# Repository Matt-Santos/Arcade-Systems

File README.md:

# Arcade Systems

A collection of custom hardware, software, and artwork for my arcade projects. It includes several retro-inspired builds using modern hardware as well as a few modifications to repair/improve functionality on older commercial systems. 

As of 2025 my arcade includes the following items:

## Custom Designs
- Pinball Magic (2022)
- Pedistal (2021)
- Countertop (2020)
- Cocktail (2019)

## Commercial Pinballs
- [Secret Service](https://www.ipdb.org/machine.cgi?id=2090) (Data East, 1988)
- [Escape from the Lost World](https://www.ipdb.org/machine.cgi?id=789) (Bally, 1988)
- [Farfalla](https://www.ipdb.org/machine.cgi?id=824) (Zaccaria, 1983)
- [SlugFest](https://www.ipdb.org/machine.cgi?id=3281) (Williams, 1991)
- [Prospector](https://www.ipdb.org/machine.cgi?id=1871) (Segasa, 1977)
- [Captain Fantastic](https://www.ipdb.org/machine.cgi?id=438) (Bally, 1976)
- [Geisha](https://www.ipdb.org/machine.cgi?id=994) (Playmatic, 1973)

## Jukeboxes
- Rockola 488 Sunset Gold (Rockola, 1982)
- Satellite 200 (NSM Music, 1982)

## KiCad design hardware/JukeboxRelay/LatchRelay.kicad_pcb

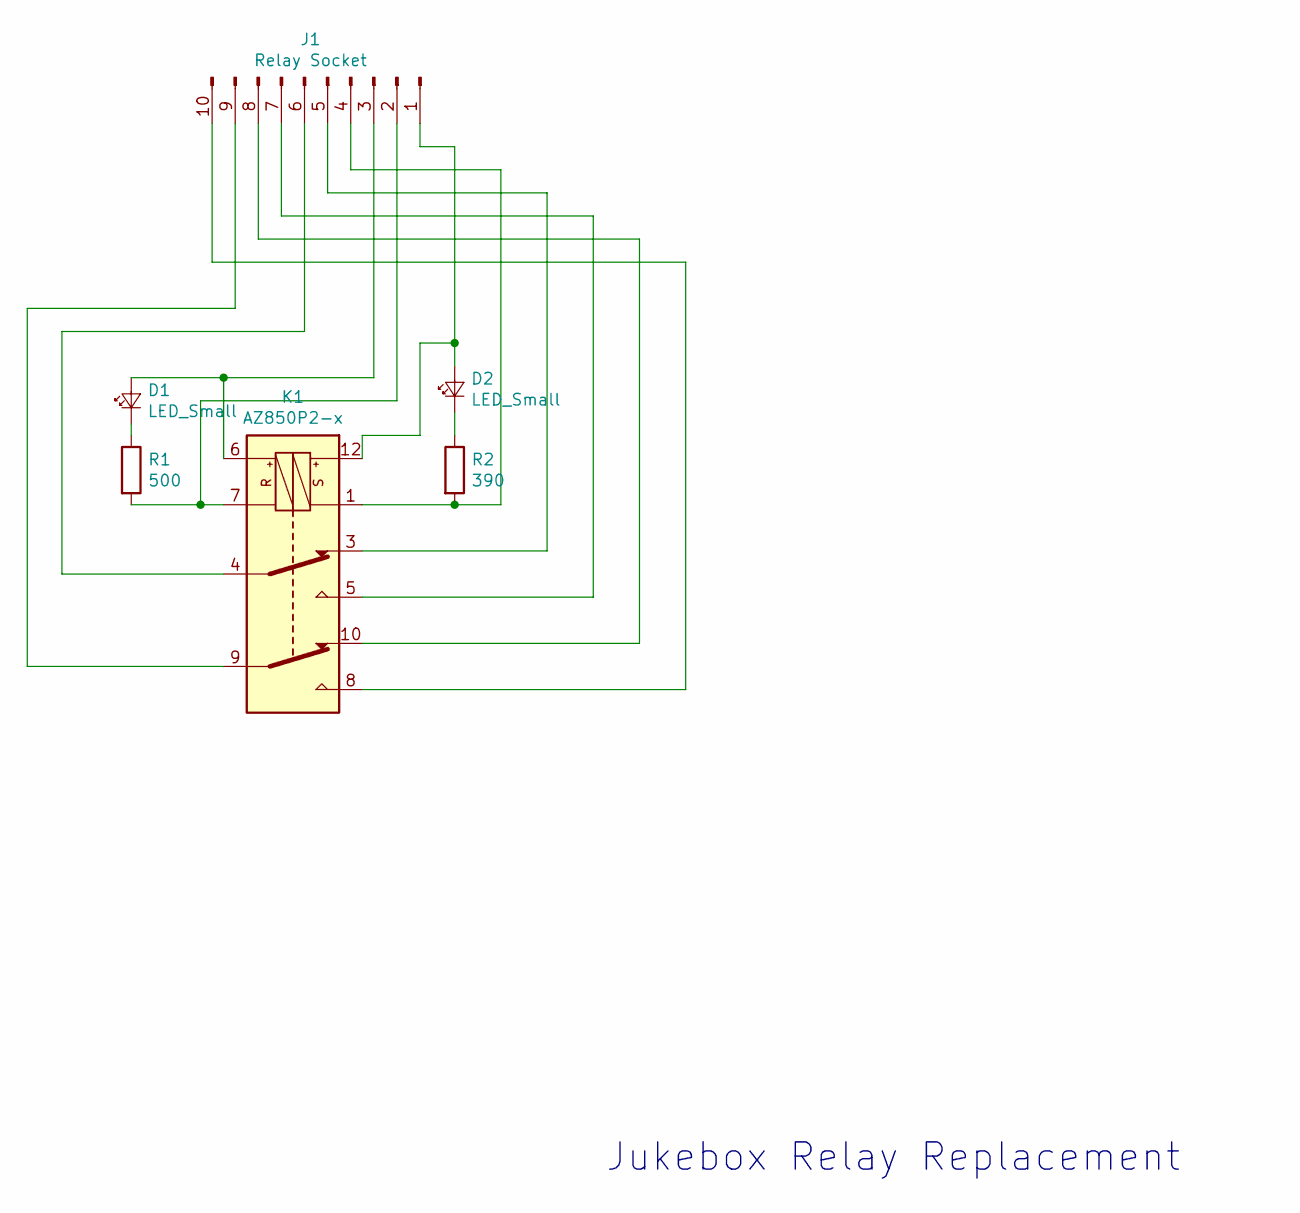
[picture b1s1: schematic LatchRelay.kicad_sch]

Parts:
D1, D2: LED_Small; LED_D4.0mm
J1: Relay Socket; Terminal_Block_Relay
K1: AZ850P2-x; Relay
R1: 500; 42J500E
R2: 390; FMP200JR-52-390R

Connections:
unnamed: D1.1 (K), R1.1
unnamed: D1.2 (A), J1.3, K1.6
unnamed: D2.1 (K), R2.1
unnamed: D2.2 (A), J1.1, K1.12
unnamed: J1.2, K1.7, R1.2
unnamed: J1.4, K1.1, R2.2
unnamed: J1.5, K1.3
unnamed: J1.6, K1.4
unnamed: J1.7, K1.5
unnamed: J1.8, K1.10
unnamed: J1.9, K1.9
unnamed: J1.10, K1.8

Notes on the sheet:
Jukebox Relay Replacement

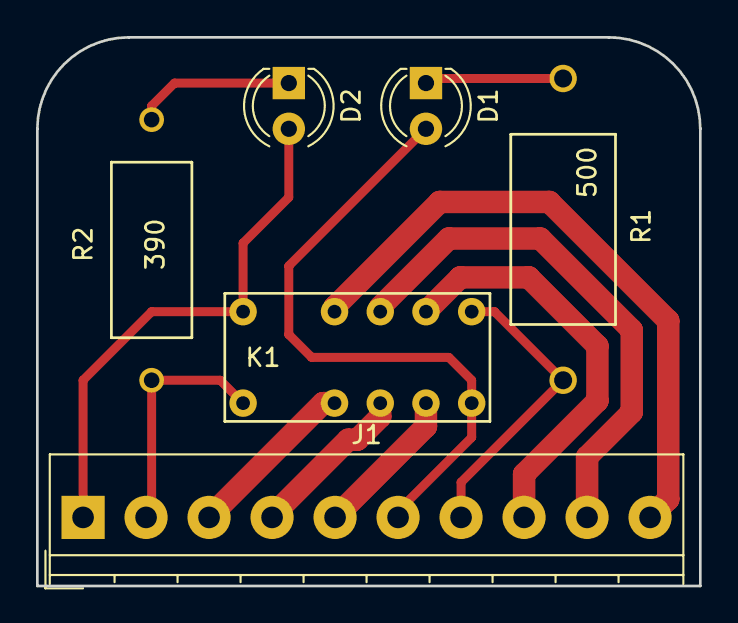
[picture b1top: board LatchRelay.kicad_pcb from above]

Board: 2 copper layers, 36.8 x 30.5 mm, 6 parts (0 on the bottom side), 12 nets.

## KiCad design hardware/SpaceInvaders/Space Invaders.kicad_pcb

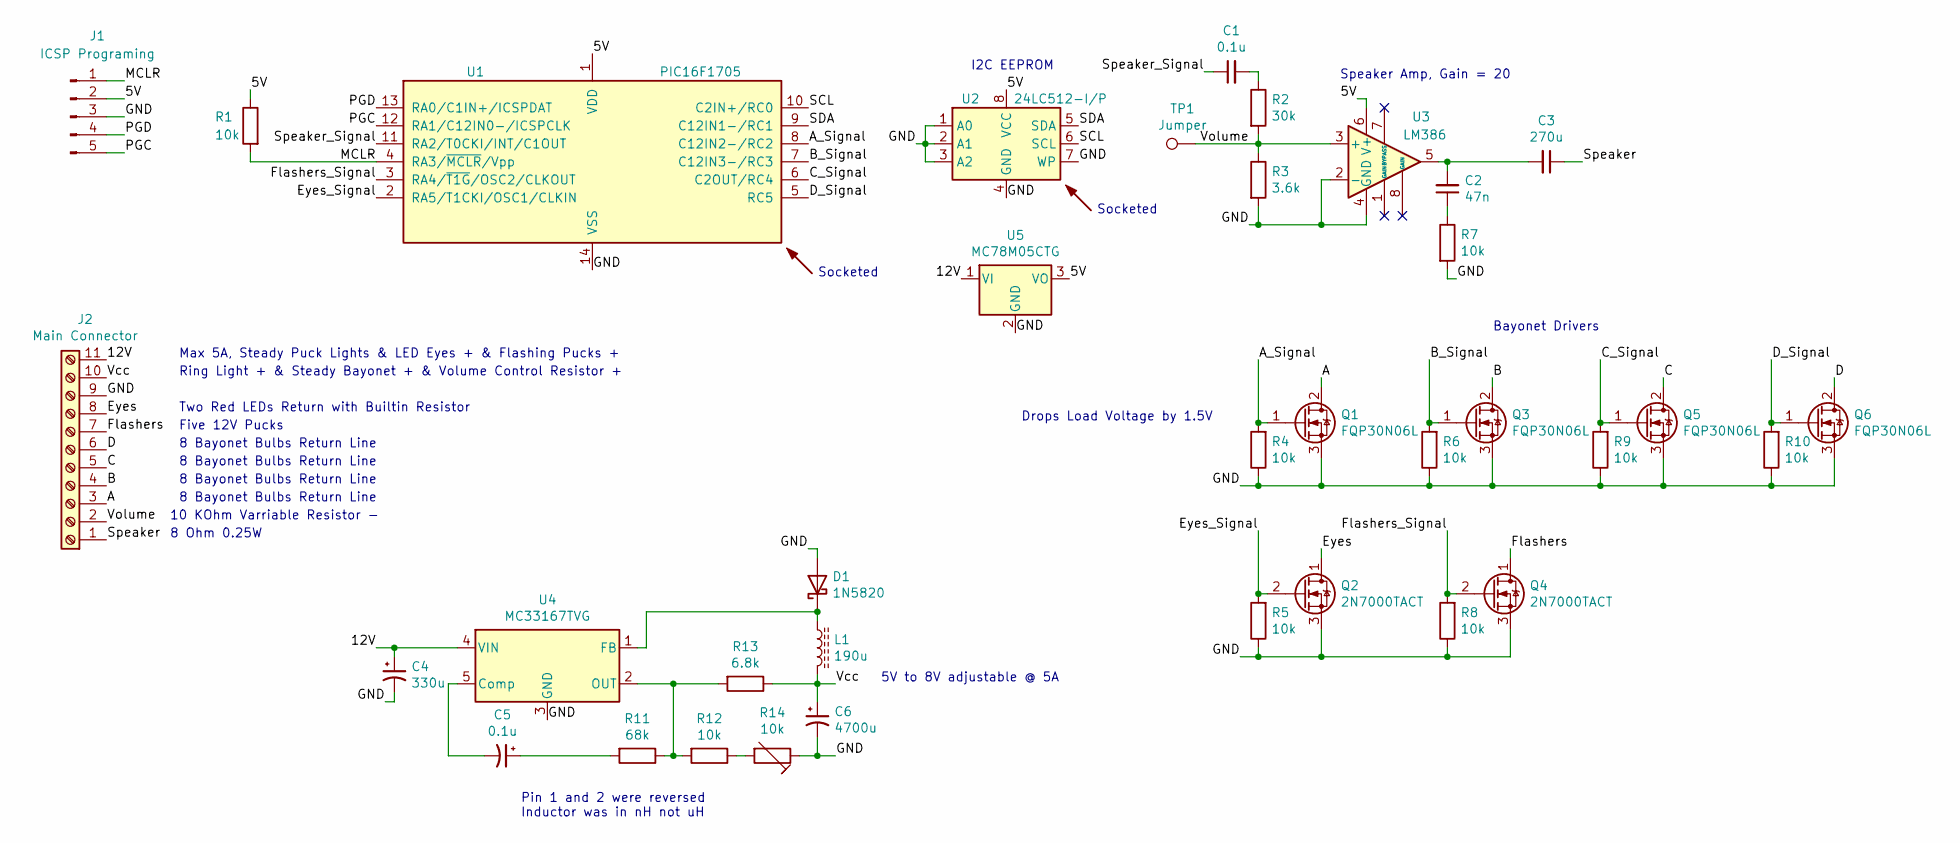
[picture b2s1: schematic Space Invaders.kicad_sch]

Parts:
C1, C5: 0.1u; C_Disc_D3.8mm_W2.6mm_P2.50mm; Digikey 399-4151-ND
C2: 47n; C_Disc_D4.7mm_W2.5mm_P5.00mm; Digikey BC2686CT-ND
C3: 270u; CP_Radial_D8.0mm_P3.50mm; Digikey 493-5019-1-ND
C4: 330u; CP_Radial_D10.0mm_P5.00mm; Digikey 493-7053-1-ND
C6: 4700u; CP_Radial_D12.5mm_P5.00mm; Digikey 1189-1123-ND
D1: 1N5820; D_DO-201AD_P15.24mm_Horizontal; Digikey 1N5820-TPMSCT-ND
J1: ICSP Programing; PinHeader_1x05_P2.54mm_Vertical; Digikey WM19491-ND
J2: Main Connector; TerminalBlock_Phoenix_MKDS-3-11-5.08_1x11_P5.08mm_Horizontal; Digikey 277-1586-ND
L1: 190u; L_Axial_L9.5mm_D4.0mm_P15.24mm_Horizontal_Fastron_SMCC; Digikey 495-76015-1-ND
Q1, Q3, Q5, Q6: FQP30N06L; TO-220-3_Vertical; Digikey FQP30N06L-ND
Q2, Q4: 2N7000TACT; TO-92_Inline; Digikey 2N7000TACT-ND
R1, R4, R5, R6, R7, R8, R9, R10, R12: 10k; R_Axial_DIN0207_L6.3mm_D2.5mm_P10.16mm_Horizontal; Digikey 13-MFR50SFTE52-10KCT-ND
R2: 30k; R_Axial_DIN0207_L6.3mm_D2.5mm_P10.16mm_Horizontal; Digikey 13-MFR-25FTE52-30KCT-ND
R3: 3.6k; R_Axial_DIN0207_L6.3mm_D2.5mm_P10.16mm_Horizontal; Digikey 13-MFR-25FTE52-3K6CT-ND
R11: 68k; R_Axial_DIN0207_L6.3mm_D2.5mm_P10.16mm_Horizontal; Digikey 13-MFR-25FTE52-68KCT-ND
R13: 6.8k; R_Axial_DIN0207_L6.3mm_D2.5mm_P10.16mm_Horizontal; Digikey 13-MFR-25FRF52-6K8CT-ND
R14: 10k; Potentiometer_Bourns_3386P_Vertical; Digikey 3362R-103LF-ND
SYM1: Socket; Digikey AE9989-ND
SYM2: Socket; Digikey AE9986-ND
TP1: Jumper; TestPoint_THTPad_D3.0mm_Drill1.5mm
U1: PIC16F1705; DIP-14_W7.62mm; Digikey PIC16F1705-I/P-ND
U2: 24LC512-I/P; DIP-8_W7.62mm; Digikey 24LC512-I/P-ND
U3: LM386; DIP-8_W7.62mm; Digikey 296-44414-5-ND
U4: MC33167TVG; TO-220-5_Vertical; Digikey MC33167TVGOS-ND
U5: MC78M05CTG; TO-220-3_Vertical; Digikey MC78M05BTGOS-ND

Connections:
/5V: J1.2, R1.1, U1.1 (VDD), U2.8 (VCC), U3.6 (V+), U5.3 (VO)
/12V: C4.1, J2.11, U4.4 (VIN), U5.1 (VI)
/A: J2.3, Q1.2 (D)
/A_Signal: Q1.1 (G), R4.2, U1.8 (C12IN2-/RC2)
/B: J2.4, Q3.2 (D)
/B_Signal: Q3.1 (G), R6.2, U1.7 (C12IN3-/RC3)
/C: J2.5, Q5.2 (D)
/C_Signal: Q5.1 (G), R9.2, U1.6 (C2OUT/RC4)
/D: J2.6, Q6.2 (D)
/D_Signal: Q6.1 (G), R10.2, U1.5 (RC5)
/Eyes: J2.8, Q2.1 (D)
/Eyes_Signal: Q2.2 (G), R5.2, U1.2 (RA5/T1CKI/OSC1/CLKIN)
/Flashers: J2.7, Q4.1 (D)
/Flashers_Signal: Q4.2 (G), R8.2, U1.3 (RA4/~T1G/OSC2/CLKOUT)
/GND: C4.2, C6.2, D1.2 (A), J1.3, J2.9, Q1.3 (S), Q2.3 (S), Q3.3 (S), Q4.3 (S), Q5.3 (S), Q6.3 (S), R3.2, R4.1, R5.1, R6.1, R7.2, R8.1, R9.1, R10.1, R14.1, U1.14 (VSS), U2.1 (A0), U2.2 (A1), U2.3 (A2), U2.4 (GND), U2.7 (WP), U3.2 (-), U3.4 (GND), U4.3 (GND), U5.2 (GND)
/MCLR: J1.1, R1.2, U1.4 (RA3/~MCLR/Vpp)
/PGC: J1.5, U1.12 (RA1/C12IN0-/ICSPCLK)
/PGD: J1.4, U1.13 (RA0/C1IN+/ICSPDAT)
/SCL: U1.10 (C2IN+/RC0), U2.6 (SCL)
/SDA: U1.9 (C12IN1-/RC1), U2.5 (SDA)
/Speaker: C3.1, J2.1
/Speaker_Signal: C1.1, U1.11 (RA2/T0CKI/INT/C1OUT)
/Vcc: C6.1, J2.10, L1.2, R13.1
/Volume: J2.2, R2.2, R3.1, TP1.1, U3.3 (+)
unnamed: C1.2, R2.1
unnamed: C2.1, R7.1
unnamed: C2.2, C3.2, U3.5
unnamed: C5.1, R11.2
unnamed: C5.2, U4.5 (Comp)
unnamed: D1.1 (K), L1.1, U4.1 (FB)
unnamed: R11.1, R12.2, R13.2, U4.2 (OUT)
unnamed: R12.1, R14.2

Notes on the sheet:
I2C EEPROM
Speaker Amp, Gain = 20
5V to 8V adjustable @ 5A
Five 12V Pucks
8 Bayonet Bulbs Return Line
Socketed
10 KOhm Varriable Resistor -
Two Red LEDs Return with Builtin Resistor
8 Ohm 0.25W
Bayonet Drivers
Ring Light + & Steady Bayonet + & Volume Control Resistor +
Pin 1 and 2 were reversed Inductor was in nH not uH
Max 5A, Steady Puck Lights & LED Eyes + & Flashing Pucks +
Drops Load Voltage by 1.5V

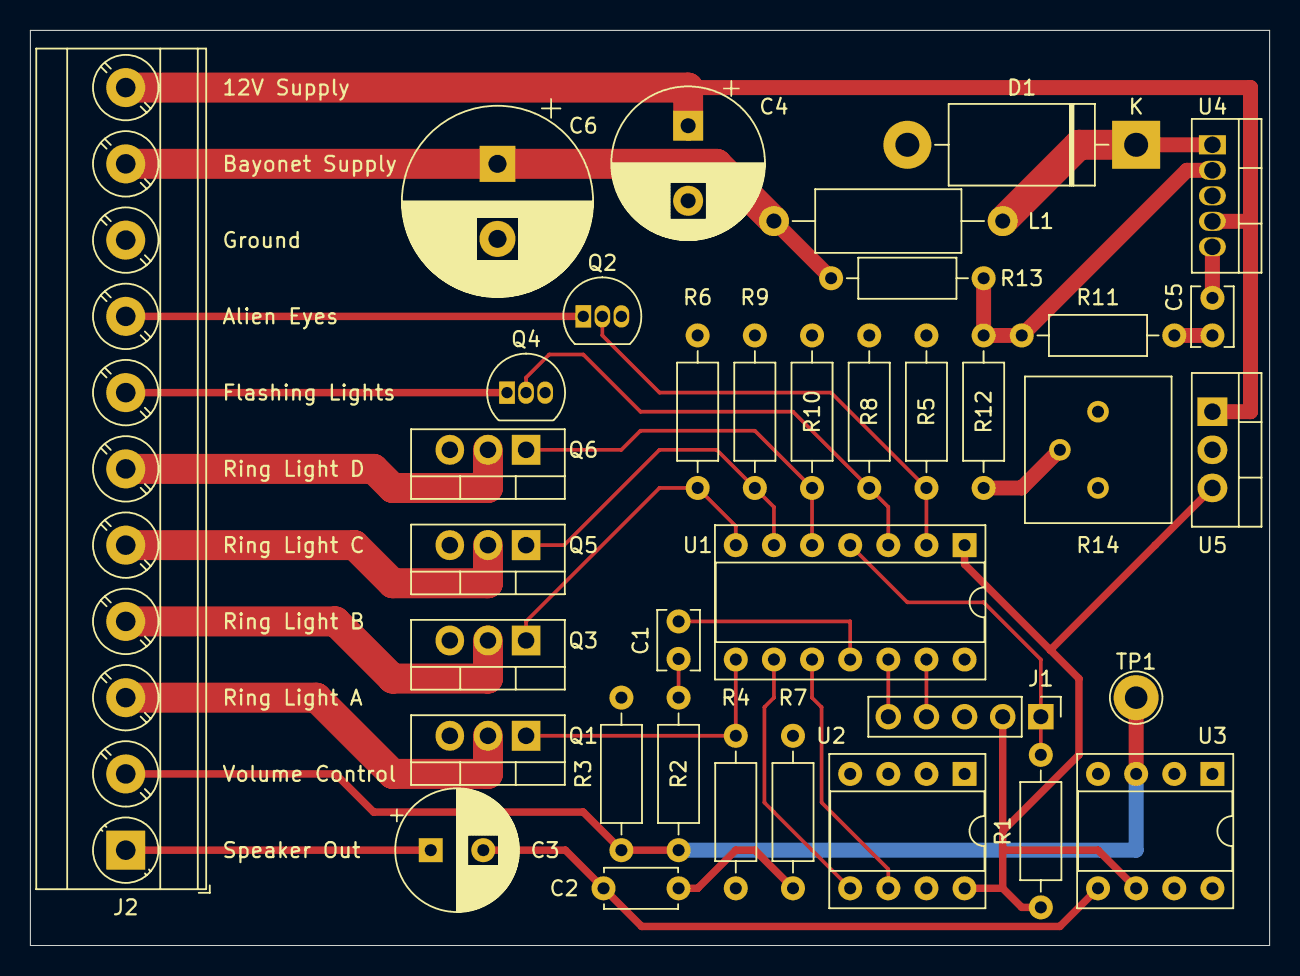
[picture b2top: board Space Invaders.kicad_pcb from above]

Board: 2 copper layers, 82.6 x 61.0 mm, 36 parts (0 on the bottom side), 32 nets.

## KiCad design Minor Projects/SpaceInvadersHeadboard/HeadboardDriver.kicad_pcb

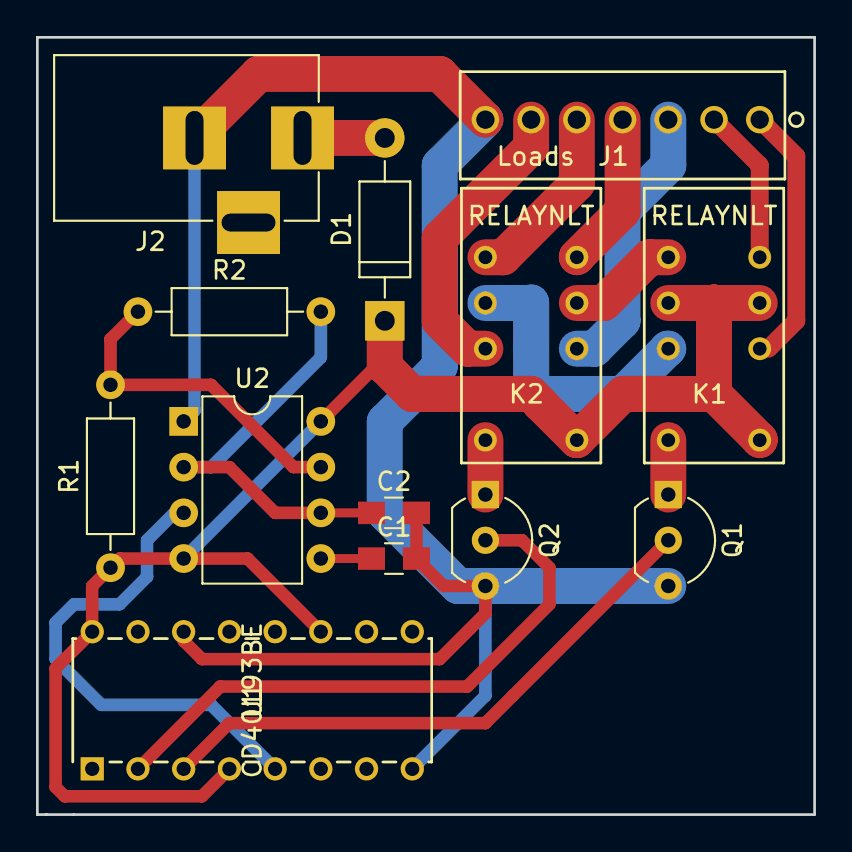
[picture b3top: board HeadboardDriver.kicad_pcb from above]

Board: 2 copper layers, 43.2 x 43.2 mm, 13 parts (0 on the bottom side), 19 nets.

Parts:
C1: 0.01u; C_0805_HandSoldering
C2: 10u; C_0805_HandSoldering
D1: MUR2100ERLGOSCT-ND; D_DO-41_SOD81_P10.16mm_Horizontal
J1: Loads; 640456-7
J2: Conn_Coaxial_Power; BARREL_JACK
K1, K2: RELAYNLT; EC2-5NU
Q1, Q2: 2N7000TACT-ND; TO-92_Inline_Wide
R1: 5.6k; R_Axial_DIN0207_L6.3mm_D2.5mm_P10.16mm_Horizontal
R2: 33k; R_Axial_DIN0207_L6.3mm_D2.5mm_P10.16mm_Horizontal
U1: CD40193BE
U2: LM555; DIP-8_W7.62mm

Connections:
0: C1.2, C2.2, J1.7, J2.2, Q1.3, Q2.3, U1.8, U1.14, U2.1
/A: J1.3, K2.3
/B: J1.4, K2.5
/C: J1.5, K2.8
/C1: Q1.2, U1.3
/C2: Q2.2, U1.2
/D: J1.6, K2.10
/Vcc: D1.1, K1.1, K1.4, K1.9, K2.1, R1.1, U1.4, U1.11, U1.16, U2.4, U2.8
/X: J1.1, K1.3
/Y: J1.2, K1.5
unnamed: C1.1, U2.5
unnamed: C2.1, R2.2, U2.2, U2.6
unnamed: D1.2, J2.1
unnamed: K1.8, K2.4
unnamed: K1.10, K2.9
unnamed: K1.12, Q1.1
unnamed: K2.12, Q2.1
unnamed: R1.2, R2.1, U2.7
unnamed: U1.5, U2.3

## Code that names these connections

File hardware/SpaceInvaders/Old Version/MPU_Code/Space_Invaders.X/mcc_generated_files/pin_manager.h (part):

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#define RA2_SetHigh()            do { LATAbits.LATA2 = 1; } while(0)
#define RA2_SetLow()             do { LATAbits.LATA2 = 0; } while(0)
#define RA2_Toggle()             do { LATAbits.LATA2 = ~LATAbits.LATA2; } while(0)
#define RA2_GetValue()              PORTAbits.RA2
#define RA2_SetDigitalInput()    do { TRISAbits.TRISA2 = 1; } while(0)
#define RA2_SetDigitalOutput()   do { TRISAbits.TRISA2 = 0; } while(0)
#define RA2_SetPullup()             do { WPUAbits.WPUA2 = 1; } while(0)
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// get/set Flashers aliases
#define Flashers_TRIS                 TRISAbits.TRISA4
#define Flashers_LAT                  LATAbits.LATA4
#define Flashers_PORT                 PORTAbits.RA4
#define Flashers_WPU                  WPUAbits.WPUA4
#define Flashers_OD                   ODCONAbits.ODA4
#define Flashers_ANS                  ANSELAbits.ANSA4
#define Flashers_SetHigh()            do { LATAbits.LATA4 = 1; } while(0)
#define Flashers_SetLow()             do { LATAbits.LATA4 = 0; } while(0)
#define Flashers_Toggle()             do { LATAbits.LATA4 = ~LATAbits.LATA4; } while(0)
#define Flashers_GetValue()           PORTAbits.RA4
#define Flashers_SetDigitalInput()    do { TRISAbits.TRISA4 = 1; } while(0)
#define Flashers_SetDigitalOutput()   do { TRISAbits.TRISA4 = 0; } while(0)
#define Flashers_SetPullup()          do { WPUAbits.WPUA4 = 1; } while(0)
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// get/set Eyes aliases
#define Eyes_TRIS                 TRISAbits.TRISA5
#define Eyes_LAT                  LATAbits.LATA5
#define Eyes_PORT                 PORTAbits.RA5
#define Eyes_WPU                  WPUAbits.WPUA5
#define Eyes_OD                   ODCONAbits.ODA5
#define Eyes_SetHigh()            do { LATAbits.LATA5 = 1; } while(0)
#define Eyes_SetLow()             do { LATAbits.LATA5 = 0; } while(0)
#define Eyes_Toggle()             do { LATAbits.LATA5 = ~LATAbits.LATA5; } while(0)
#define Eyes_GetValue()           PORTAbits.RA5
#define Eyes_SetDigitalInput()    do { TRISAbits.TRISA5 = 1; } while(0)
#define Eyes_SetDigitalOutput()   do { TRISAbits.TRISA5 = 0; } while(0)
#define Eyes_SetPullup()          do { WPUAbits.WPUA5 = 1; } while(0)
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// get/set scl aliases
#define scl_TRIS                 TRISCbits.TRISC0
#define scl_LAT                  LATCbits.LATC0
#define scl_PORT                 PORTCbits.RC0
#define scl_WPU                  WPUCbits.WPUC0
#define scl_OD                   ODCONCbits.ODC0
#define scl_ANS                  ANSELCbits.ANSC0
#define scl_SetHigh()            do { LATCbits.LATC0 = 1; } while(0)
#define scl_SetLow()             do { LATCbits.LATC0 = 0; } while(0)
#define scl_Toggle()             do { LATCbits.LATC0 = ~LATCbits.LATC0; } while(0)
#define scl_GetValue()           PORTCbits.RC0
#define scl_SetDigitalInput()    do { TRISCbits.TRISC0 = 1; } while(0)
#define scl_SetDigitalOutput()   do { TRISCbits.TRISC0 = 0; } while(0)
#define scl_SetPullup()          do { WPUCbits.WPUC0 = 1; } while(0)
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// get/set sda aliases
#define sda_TRIS                 TRISCbits.TRISC1
#define sda_LAT                  LATCbits.LATC1
#define sda_PORT                 PORTCbits.RC1
#define sda_WPU                  WPUCbits.WPUC1
#define sda_OD                   ODCONCbits.ODC1
#define sda_ANS                  ANSELCbits.ANSC1
#define sda_SetHigh()            do { LATCbits.LATC1 = 1; } while(0)
#define sda_SetLow()             do { LATCbits.LATC1 = 0; } while(0)
#define sda_Toggle()             do { LATCbits.LATC1 = ~LATCbits.LATC1; } while(0)
#define sda_GetValue()           PORTCbits.RC1
#define sda_SetDigitalInput()    do { TRISCbits.TRISC1 = 1; } while(0)
#define sda_SetDigitalOutput()   do { TRISCbits.TRISC1 = 0; } while(0)
#define sda_SetPullup()          do { WPUCbits.WPUC1 = 1; } while(0)
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// get/set A_Signal aliases
#define A_Signal_TRIS                 TRISCbits.TRISC2
#define A_Signal_LAT                  LATCbits.LATC2
#define A_Signal_PORT                 PORTCbits.RC2
#define A_Signal_WPU                  WPUCbits.WPUC2
#define A_Signal_OD                   ODCONCbits.ODC2
#define A_Signal_ANS                  ANSELCbits.ANSC2
#define A_Signal_SetHigh()            do { LATCbits.LATC2 = 1; } while(0)
#define A_Signal_SetLow()             do { LATCbits.LATC2 = 0; } while(0)
#define A_Signal_Toggle()             do { LATCbits.LATC2 = ~LATCbits.LATC2; } while(0)
#define A_Signal_GetValue()           PORTCbits.RC2
#define A_Signal_SetDigitalInput()    do { TRISCbits.TRISC2 = 1; } while(0)
#define A_Signal_SetDigitalOutput()   do { TRISCbits.TRISC2 = 0; } while(0)
#define A_Signal_SetPullup()          do { WPUCbits.WPUC2 = 1; } while(0)
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// get/set B_Signal aliases
#define B_Signal_TRIS                 TRISCbits.TRISC3
#define B_Signal_LAT                  LATCbits.LATC3
#define B_Signal_PORT                 PORTCbits.RC3
#define B_Signal_WPU                  WPUCbits.WPUC3
#define B_Signal_OD                   ODCONCbits.ODC3
#define B_Signal_ANS                  ANSELCbits.ANSC3
#define B_Signal_SetHigh()            do { LATCbits.LATC3 = 1; } while(0)
#define B_Signal_SetLow()             do { LATCbits.LATC3 = 0; } while(0)
#define B_Signal_Toggle()             do { LATCbits.LATC3 = ~LATCbits.LATC3; } while(0)
#define B_Signal_GetValue()           PORTCbits.RC3
#define B_Signal_SetDigitalInput()    do { TRISCbits.TRISC3 = 1; } while(0)
#define B_Signal_SetDigitalOutput()   do { TRISCbits.TRISC3 = 0; } while(0)
#define B_Signal_SetPullup()          do { WPUCbits.WPUC3 = 1; } while(0)
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// get/set C_Signal aliases
#define C_Signal_TRIS                 TRISCbits.TRISC4
#define C_Signal_LAT                  LATCbits.LATC4
#define C_Signal_PORT                 PORTCbits.RC4
#define C_Signal_WPU                  WPUCbits.WPUC4
#define C_Signal_OD                   ODCONCbits.ODC4
#define C_Signal_ANS                  ANSELCbits.ANSC4
#define C_Signal_SetHigh()            do { LATCbits.LATC4 = 1; } while(0)
#define C_Signal_SetLow()             do { LATCbits.LATC4 = 0; } while(0)
#define C_Signal_Toggle()             do { LATCbits.LATC4 = ~LATCbits.LATC4; } while(0)
#define C_Signal_GetValue()           PORTCbits.RC4
#define C_Signal_SetDigitalInput()    do { TRISCbits.TRISC4 = 1; } while(0)
#define C_Signal_SetDigitalOutput()   do { TRISCbits.TRISC4 = 0; } while(0)
#define C_Signal_SetPullup()          do { WPUCbits.WPUC4 = 1; } while(0)
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// get/set D_Signal aliases
#define D_Signal_TRIS                 TRISCbits.TRISC5
#define D_Signal_LAT                  LATCbits.LATC5
#define D_Signal_PORT                 PORTCbits.RC5
#define D_Signal_WPU                  WPUCbits.WPUC5
#define D_Signal_OD                   ODCONCbits.ODC5
#define D_Signal_ANS                  ANSELCbits.ANSC5
#define D_Signal_SetHigh()            do { LATCbits.LATC5 = 1; } while(0)
#define D_Signal_SetLow()             do { LATCbits.LATC5 = 0; } while(0)
#define D_Signal_Toggle()             do { LATCbits.LATC5 = ~LATCbits.LATC5; } while(0)
#define D_Signal_GetValue()           PORTCbits.RC5
#define D_Signal_SetDigitalInput()    do { TRISCbits.TRISC5 = 1; } while(0)
#define D_Signal_SetDigitalOutput()   do { TRISCbits.TRISC5 = 0; } while(0)
#define D_Signal_SetPullup()          do { WPUCbits.WPUC5 = 1; } while(0)
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
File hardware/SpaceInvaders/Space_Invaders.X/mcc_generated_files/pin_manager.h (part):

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// get/set IO_RA0 aliases
#define IO_RA0_TRIS                 TRISAbits.TRISA0
#define IO_RA0_LAT                  LATAbits.LATA0
#define IO_RA0_PORT                 PORTAbits.RA0
#define IO_RA0_WPU                  WPUAbits.WPUA0
#define IO_RA0_OD                   ODCONAbits.ODA0
#define IO_RA0_ANS                  ANSELAbits.ANSA0
#define IO_RA0_SetHigh()            do { LATAbits.LATA0 = 1; } while(0)
#define IO_RA0_SetLow()             do { LATAbits.LATA0 = 0; } while(0)
#define IO_RA0_Toggle()             do { LATAbits.LATA0 = ~LATAbits.LATA0; } while(0)
#define IO_RA0_GetValue()           PORTAbits.RA0
#define IO_RA0_SetDigitalInput()    do { TRISAbits.TRISA0 = 1; } while(0)
#define IO_RA0_SetDigitalOutput()   do { TRISAbits.TRISA0 = 0; } while(0)
#define IO_RA0_SetPullup()          do { WPUAbits.WPUA0 = 1; } while(0)
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// get/set IO_RA1 aliases
#define IO_RA1_TRIS                 TRISAbits.TRISA1
#define IO_RA1_LAT                  LATAbits.LATA1
#define IO_RA1_PORT                 PORTAbits.RA1
#define IO_RA1_WPU                  WPUAbits.WPUA1
#define IO_RA1_OD                   ODCONAbits.ODA1
#define IO_RA1_ANS                  ANSELAbits.ANSA1
#define IO_RA1_SetHigh()            do { LATAbits.LATA1 = 1; } while(0)
#define IO_RA1_SetLow()             do { LATAbits.LATA1 = 0; } while(0)
#define IO_RA1_Toggle()             do { LATAbits.LATA1 = ~LATAbits.LATA1; } while(0)
#define IO_RA1_GetValue()           PORTAbits.RA1
#define IO_RA1_SetDigitalInput()    do { TRISAbits.TRISA1 = 1; } while(0)
#define IO_RA1_SetDigitalOutput()   do { TRISAbits.TRISA1 = 0; } while(0)
#define IO_RA1_SetPullup()          do { WPUAbits.WPUA1 = 1; } while(0)
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// get/set IO_RA2 aliases
#define IO_RA2_TRIS                 TRISAbits.TRISA2
#define IO_RA2_LAT                  LATAbits.LATA2
#define IO_RA2_PORT                 PORTAbits.RA2
#define IO_RA2_WPU                  WPUAbits.WPUA2
#define IO_RA2_OD                   ODCONAbits.ODA2
#define IO_RA2_ANS                  ANSELAbits.ANSA2
#define IO_RA2_SetHigh()            do { LATAbits.LATA2 = 1; } while(0)
#define IO_RA2_SetLow()             do { LATAbits.LATA2 = 0; } while(0)
#define IO_RA2_Toggle()             do { LATAbits.LATA2 = ~LATAbits.LATA2; } while(0)
#define IO_RA2_GetValue()           PORTAbits.RA2
#define IO_RA2_SetDigitalInput()    do { TRISAbits.TRISA2 = 1; } while(0)
#define IO_RA2_SetDigitalOutput()   do { TRISAbits.TRISA2 = 0; } while(0)
#define IO_RA2_SetPullup()          do { WPUAbits.WPUA2 = 1; } while(0)
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// get/set channel_AN3 aliases
#define channel_AN3_TRIS                 TRISAbits.TRISA4
#define channel_AN3_LAT                  LATAbits.LATA4
#define channel_AN3_PORT                 PORTAbits.RA4
#define channel_AN3_WPU                  WPUAbits.WPUA4
#define channel_AN3_OD                   ODCONAbits.ODA4
#define channel_AN3_ANS                  ANSELAbits.ANSA4
#define channel_AN3_SetHigh()            do { LATAbits.LATA4 = 1; } while(0)
#define channel_AN3_SetLow()             do { LATAbits.LATA4 = 0; } while(0)
#define channel_AN3_Toggle()             do { LATAbits.LATA4 = ~LATAbits.LATA4; } while(0)
#define channel_AN3_GetValue()           PORTAbits.RA4
#define channel_AN3_SetDigitalInput()    do { TRISAbits.TRISA4 = 1; } while(0)
#define channel_AN3_SetDigitalOutput()   do { TRISAbits.TRISA4 = 0; } while(0)
#define channel_AN3_SetPullup()          do { WPUAbits.WPUA4 = 1; } while(0)
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// get/set IO_RA5 aliases
#define IO_RA5_TRIS                 TRISAbits.TRISA5
#define IO_RA5_LAT                  LATAbits.LATA5
#define IO_RA5_PORT                 PORTAbits.RA5
#define IO_RA5_WPU                  WPUAbits.WPUA5
#define IO_RA5_OD                   ODCONAbits.ODA5
#define IO_RA5_SetHigh()            do { LATAbits.LATA5 = 1; } while(0)
#define IO_RA5_SetLow()             do { LATAbits.LATA5 = 0; } while(0)
#define IO_RA5_Toggle()             do { LATAbits.LATA5 = ~LATAbits.LATA5; } while(0)
#define IO_RA5_GetValue()           PORTAbits.RA5
#define IO_RA5_SetDigitalInput()    do { TRISAbits.TRISA5 = 1; } while(0)
#define IO_RA5_SetDigitalOutput()   do { TRISAbits.TRISA5 = 0; } while(0)
#define IO_RA5_SetPullup()          do { WPUAbits.WPUA5 = 1; } while(0)
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// get/set IO_RC0 aliases
#define IO_RC0_TRIS                 TRISCbits.TRISC0
#define IO_RC0_LAT                  LATCbits.LATC0
#define IO_RC0_PORT                 PORTCbits.RC0
#define IO_RC0_WPU                  WPUCbits.WPUC0
#define IO_RC0_OD                   ODCONCbits.ODC0
#define IO_RC0_ANS                  ANSELCbits.ANSC0
#define IO_RC0_SetHigh()            do { LATCbits.LATC0 = 1; } while(0)
#define IO_RC0_SetLow()             do { LATCbits.LATC0 = 0; } while(0)
#define IO_RC0_Toggle()             do { LATCbits.LATC0 = ~LATCbits.LATC0; } while(0)
#define IO_RC0_GetValue()           PORTCbits.RC0
#define IO_RC0_SetDigitalInput()    do { TRISCbits.TRISC0 = 1; } while(0)
#define IO_RC0_SetDigitalOutput()   do { TRISCbits.TRISC0 = 0; } while(0)
#define IO_RC0_SetPullup()          do { WPUCbits.WPUC0 = 1; } while(0)
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// get/set IO_RC1 aliases
#define IO_RC1_TRIS                 TRISCbits.TRISC1
#define IO_RC1_LAT                  LATCbits.LATC1
#define IO_RC1_PORT                 PORTCbits.RC1
#define IO_RC1_WPU                  WPUCbits.WPUC1
#define IO_RC1_OD                   ODCONCbits.ODC1
#define IO_RC1_ANS                  ANSELCbits.ANSC1
#define IO_RC1_SetHigh()            do { LATCbits.LATC1 = 1; } while(0)
#define IO_RC1_SetLow()             do { LATCbits.LATC1 = 0; } while(0)
#define IO_RC1_Toggle()             do { LATCbits.LATC1 = ~LATCbits.LATC1; } while(0)
#define IO_RC1_GetValue()           PORTCbits.RC1
#define IO_RC1_SetDigitalInput()    do { TRISCbits.TRISC1 = 1; } while(0)
#define IO_RC1_SetDigitalOutput()   do { TRISCbits.TRISC1 = 0; } while(0)
#define IO_RC1_SetPullup()          do { WPUCbits.WPUC1 = 1; } while(0)
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// get/set IO_RC2 aliases
#define IO_RC2_TRIS                 TRISCbits.TRISC2
#define IO_RC2_LAT                  LATCbits.LATC2
#define IO_RC2_PORT                 PORTCbits.RC2
#define IO_RC2_WPU                  WPUCbits.WPUC2
#define IO_RC2_OD                   ODCONCbits.ODC2
#define IO_RC2_ANS                  ANSELCbits.ANSC2
#define IO_RC2_SetHigh()            do { LATCbits.LATC2 = 1; } while(0)
#define IO_RC2_SetLow()             do { LATCbits.LATC2 = 0; } while(0)
#define IO_RC2_Toggle()             do { LATCbits.LATC2 = ~LATCbits.LATC2; } while(0)
#define IO_RC2_GetValue()           PORTCbits.RC2
#define IO_RC2_SetDigitalInput()    do { TRISCbits.TRISC2 = 1; } while(0)
#define IO_RC2_SetDigitalOutput()   do { TRISCbits.TRISC2 = 0; } while(0)
#define IO_RC2_SetPullup()          do { WPUCbits.WPUC2 = 1; } while(0)
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#define RC3_SetHigh()            do { LATCbits.LATC3 = 1; } while(0)
#define RC3_SetLow()             do { LATCbits.LATC3 = 0; } while(0)
#define RC3_Toggle()             do { LATCbits.LATC3 = ~LATCbits.LATC3; } while(0)
#define RC3_GetValue()              PORTCbits.RC3
#define RC3_SetDigitalInput()    do { TRISCbits.TRISC3 = 1; } while(0)
#define RC3_SetDigitalOutput()   do { TRISCbits.TRISC3 = 0; } while(0)
#define RC3_SetPullup()             do { WPUCbits.WPUC3 = 1; } while(0)
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// get/set IO_RC4 aliases
#define IO_RC4_TRIS                 TRISCbits.TRISC4
#define IO_RC4_LAT                  LATCbits.LATC4
#define IO_RC4_PORT                 PORTCbits.RC4
#define IO_RC4_WPU                  WPUCbits.WPUC4
#define IO_RC4_OD                   ODCONCbits.ODC4
#define IO_RC4_ANS                  ANSELCbits.ANSC4
#define IO_RC4_SetHigh()            do { LATCbits.LATC4 = 1; } while(0)
#define IO_RC4_SetLow()             do { LATCbits.LATC4 = 0; } while(0)
#define IO_RC4_Toggle()             do { LATCbits.LATC4 = ~LATCbits.LATC4; } while(0)
#define IO_RC4_GetValue()           PORTCbits.RC4
#define IO_RC4_SetDigitalInput()    do { TRISCbits.TRISC4 = 1; } while(0)
#define IO_RC4_SetDigitalOutput()   do { TRISCbits.TRISC4 = 0; } while(0)
#define IO_RC4_SetPullup()          do { WPUCbits.WPUC4 = 1; } while(0)
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// get/set IO_RC5 aliases
#define IO_RC5_TRIS                 TRISCbits.TRISC5
#define IO_RC5_LAT                  LATCbits.LATC5
#define IO_RC5_PORT                 PORTCbits.RC5
#define IO_RC5_WPU                  WPUCbits.WPUC5
#define IO_RC5_OD                   ODCONCbits.ODC5
#define IO_RC5_ANS                  ANSELCbits.ANSC5
#define IO_RC5_SetHigh()            do { LATCbits.LATC5 = 1; } while(0)
#define IO_RC5_SetLow()             do { LATCbits.LATC5 = 0; } while(0)
#define IO_RC5_Toggle()             do { LATCbits.LATC5 = ~LATCbits.LATC5; } while(0)
#define IO_RC5_GetValue()           PORTCbits.RC5
#define IO_RC5_SetDigitalInput()    do { TRISCbits.TRISC5 = 1; } while(0)
#define IO_RC5_SetDigitalOutput()   do { TRISCbits.TRISC5 = 0; } while(0)
#define IO_RC5_SetPullup()          do { WPUCbits.WPUC5 = 1; } while(0)
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
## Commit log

2017-12-24 Add in Jukebox and SpaceInvaders working files
2018-01-06 Finished Jukebox Relay Design
2018-01-08 Completed JukeBox and SpaceInvader PCBs Created Gerbers Ordered Parts
2018-01-12 Added FMCW Radar Project Files
2018-06-11 Finalized PCB Designs for Relay and Space Invaders and ordered them
2024-12-30 feat: update content
2025-01-09 feat: add project README files
2025-01-10 fix: image/artwork organization
2025-04-07 add: Space Invaders MPU Code

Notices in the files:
hardware/SpaceInvaders/Old Version/MPU_Code/Space_Invaders.X/mcc_generated_files/pin_manager.h:
(c) 2018 Microchip Technology Inc. and its subsidiaries.
